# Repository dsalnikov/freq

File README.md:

# This is a KiCad project of ESC power board 

This is a board with power MOSFETs (any TO-252), drivers (L6390), and measurement circuits for current and voltage. 
All components are quite big, so board can be hand soldered.

### Known issues:
* There is no input voltage measurement
* Input voltage capacitors are too small

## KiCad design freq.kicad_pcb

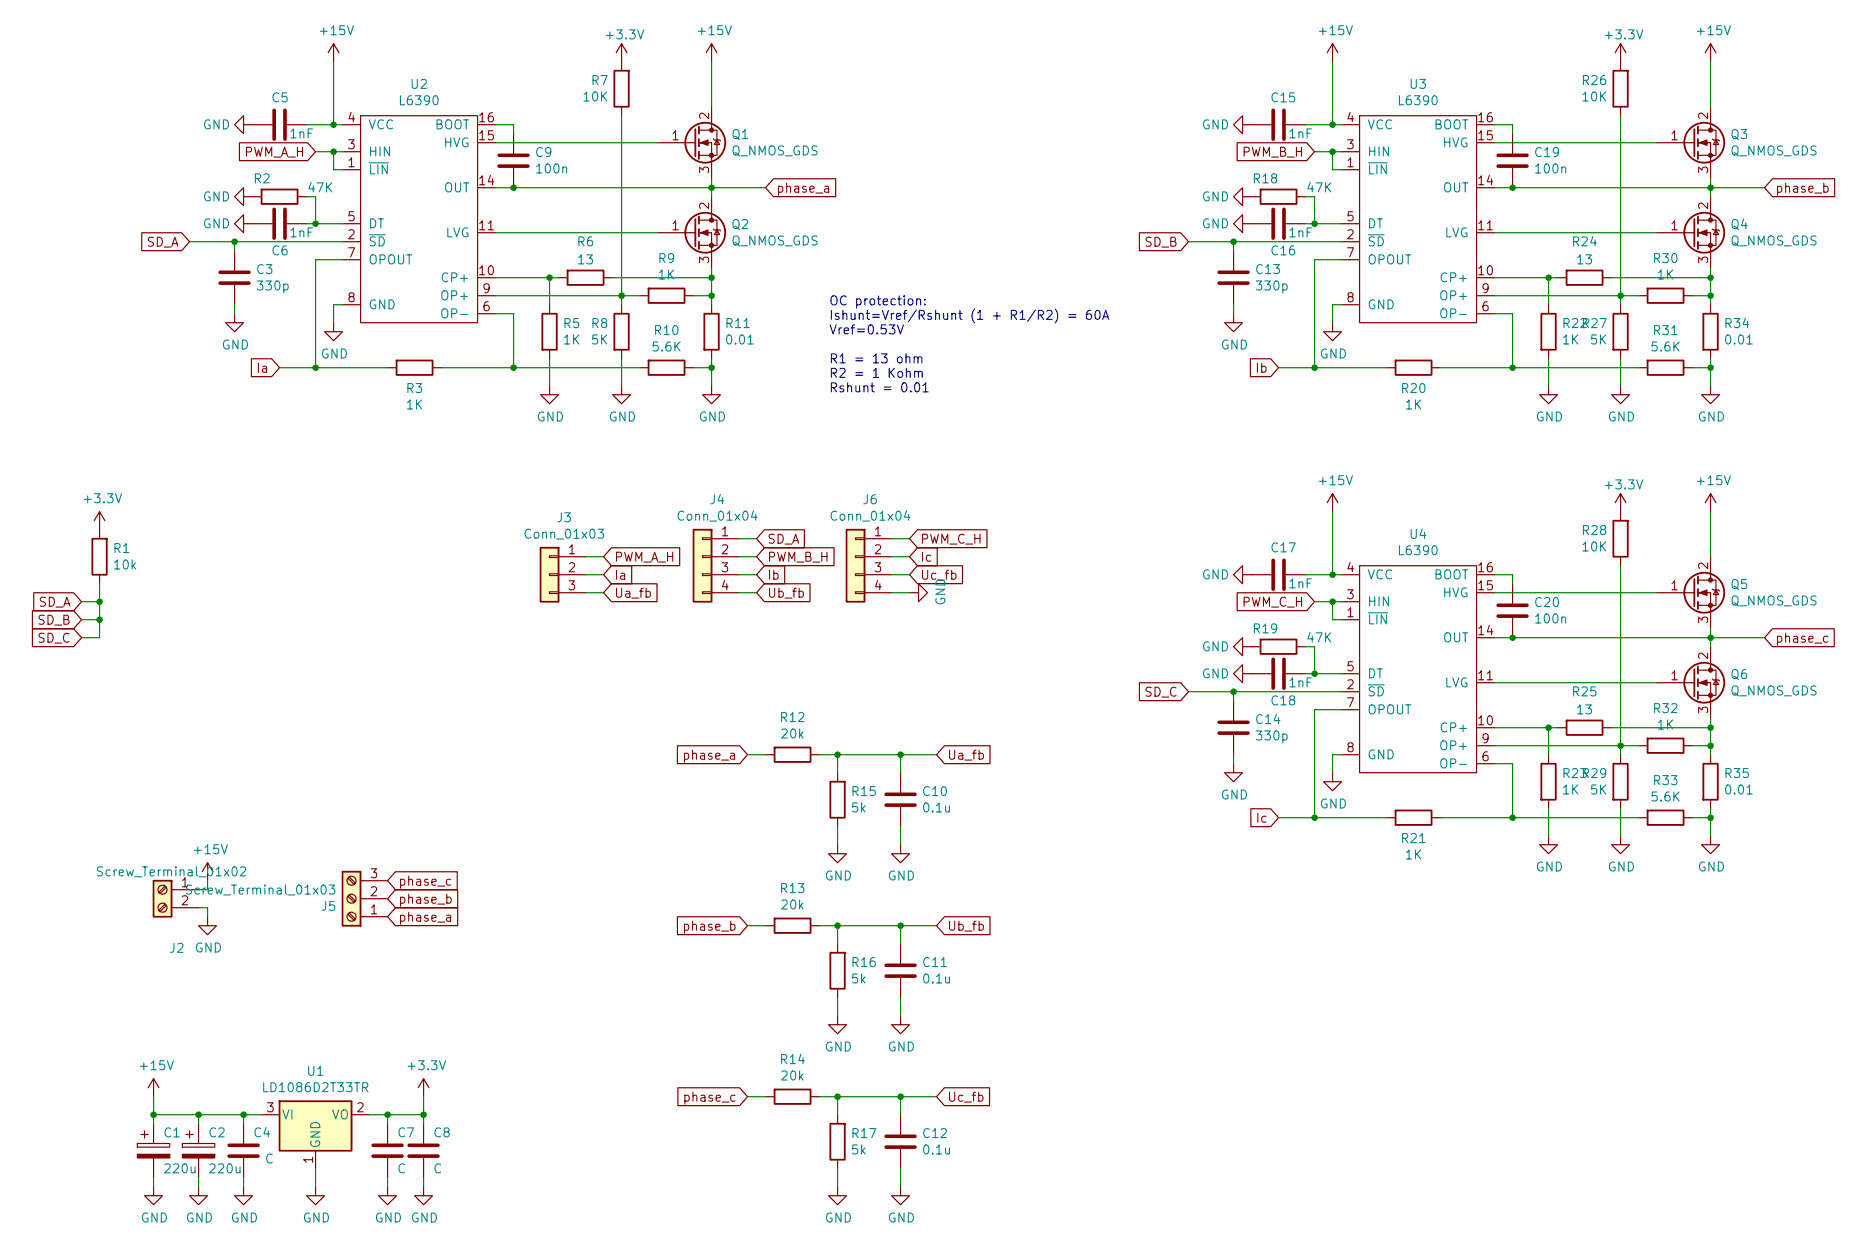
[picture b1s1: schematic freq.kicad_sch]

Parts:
C1, C2: 220u; CP_Elec_5x4.5
C3, C13, C14: 330p; C_0805_2012Metric_Pad1.15x1.40mm_HandSolder
C4, C7, C8: C; C_0805_2012Metric_Pad1.15x1.40mm_HandSolder
C5, C6, C15, C16, C17, C18: 1nF; C_0805_2012Metric_Pad1.15x1.40mm_HandSolder
C9, C19, C20: 100n; C_0805_2012Metric_Pad1.15x1.40mm_HandSolder
C10, C11, C12: 0.1u; C_0805_2012Metric_Pad1.15x1.40mm_HandSolder
J2: Screw_Terminal_01x02; TerminalBlock_Altech_AK300-2_P5.00mm
J3: Conn_01x03; PinHeader_1x03_P2.54mm_Vertical
J4, J6: Conn_01x04; PinHeader_1x04_P2.54mm_Vertical
J5: Screw_Terminal_01x03; TerminalBlock_Altech_AK300-3_P5.00mm
Q1, Q2, Q3, Q4, Q5, Q6: Q_NMOS_GDS; TO-252-2
R1: 10k; R_0805_2012Metric_Pad1.15x1.40mm_HandSolder
R2, R18, R19: 47K; R_0805_2012Metric_Pad1.15x1.40mm_HandSolder
R3, R5, R9, R20, R21, R22, R23, R30, R32: 1K; R_0805_2012Metric_Pad1.15x1.40mm_HandSolder
R6, R24, R25: 13; R_0805_2012Metric_Pad1.15x1.40mm_HandSolder
R7, R26, R28: 10K; R_0805_2012Metric_Pad1.15x1.40mm_HandSolder
R8, R27, R29: 5K; R_0805_2012Metric_Pad1.15x1.40mm_HandSolder
R10, R31, R33: 5.6K; R_0805_2012Metric_Pad1.15x1.40mm_HandSolder
R11, R34, R35: 0.01; R_2512_6332Metric_Pad1.52x3.35mm_HandSolder
R12, R13, R14: 20k; R_0805_2012Metric_Pad1.15x1.40mm_HandSolder
R15, R16, R17: 5k; R_0805_2012Metric_Pad1.15x1.40mm_HandSolder
U1: LD1086D2T33TR; SOT-223-3_TabPin2
U2, U3, U4: L6390; SOIC-16_3.9x9.9mm_P1.27mm

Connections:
+3V3: C7.1, C8.1, R1.2, R7.2, R26.2, R28.2, U1.2 (VO)
+15V: C1.1, C2.1, C4.1, C5.1, C15.1, C17.1, J2.1, Q1.2 (D), Q3.2 (D), Q5.2 (D), U1.3 (VI), U2.4 (VCC), U3.4 (VCC), U4.4 (VCC)
GND: C1.2, C2.2, C3.2, C4.2, C5.2, C6.2, C7.2, C8.2, C10.2, C11.2, C12.2, C13.2, C14.2, C15.2, C16.2, C17.2, C18.2, J2.2, J6.4, R2.2, R5.2, R8.2, R10.1, R11.2, R15.1, R16.1, R17.1, R18.2, R19.2, R22.2, R23.2, R27.2, R29.2, R31.1, R33.1, R34.2, R35.2, U1.1 (GND), U2.8 (GND), U3.8 (GND), U4.8 (GND)
Ia: J3.2, R3.2, U2.7 (OPOUT)
Ib: J4.3, R20.2, U3.7 (OPOUT)
Ic: J6.2, R21.2, U4.7 (OPOUT)
unnamed: C6.1, R2.1, U2.5 (DT)
unnamed: C9.1, U2.16 (BOOT)
unnamed: C16.1, R18.1, U3.5 (DT)
unnamed: C18.1, R19.1, U4.5 (DT)
unnamed: C19.1, U3.16 (BOOT)
unnamed: C20.1, U4.16 (BOOT)
unnamed: Q1.1 (G), U2.15 (HVG)
unnamed: Q2.1 (G), U2.11 (LVG)
unnamed: Q2.3 (S), R6.1, R9.1, R11.1
unnamed: Q3.1 (G), U3.15 (HVG)
unnamed: Q4.1 (G), U3.11 (LVG)
unnamed: Q4.3 (S), R24.1, R30.1, R34.1
unnamed: Q5.1 (G), U4.15 (HVG)
unnamed: Q6.1 (G), U4.11 (LVG)
unnamed: Q6.3 (S), R25.1, R32.1, R35.1
unnamed: R5.1, R6.2, U2.10 (CP+)
unnamed: R7.1, R8.1, R9.2, U2.9 (OP+)
unnamed: R3.1, R10.2, U2.6 (OP-)
unnamed: R20.1, R31.2, U3.6 (OP-)
unnamed: R21.1, R33.2, U4.6 (OP-)
unnamed: R22.1, R24.2, U3.10 (CP+)
unnamed: R23.1, R25.2, U4.10 (CP+)
unnamed: R26.1, R27.1, R30.2, U3.9 (OP+)
unnamed: R28.1, R29.1, R32.2, U4.9 (OP+)
PWM_A_H: J3.1, U2.1 (~LIN), U2.3 (HIN)
PWM_B_H: J4.2, U3.1 (~LIN), U3.3 (HIN)
PWM_C_H: J6.1, U4.1 (~LIN), U4.3 (HIN)
SD_A: C3.1, C13.1, C14.1, J4.1, R1.1, U2.2 (~SD), U3.2 (~SD), U4.2 (~SD)
Ua_fb: C10.1, J3.3, R12.1, R15.2
Ub_fb: C11.1, J4.4, R13.1, R16.2
Uc_fb: C12.1, J6.3, R14.1, R17.2
phase_a: C9.2, J5.1, Q1.3 (S), Q2.2 (D), R12.2, U2.14 (OUT)
phase_b: C19.2, J5.2, Q3.3 (S), Q4.2 (D), R13.2, U3.14 (OUT)
phase_c: C20.2, J5.3, Q5.3 (S), Q6.2 (D), R14.2, U4.14 (OUT)

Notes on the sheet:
OC protection: Ishunt=Vref/Rshunt (1 + R1/R2) = 60A Vref=0.53V R1 = 13 ohm R2 = 1 Kohm Rshunt = 0.01

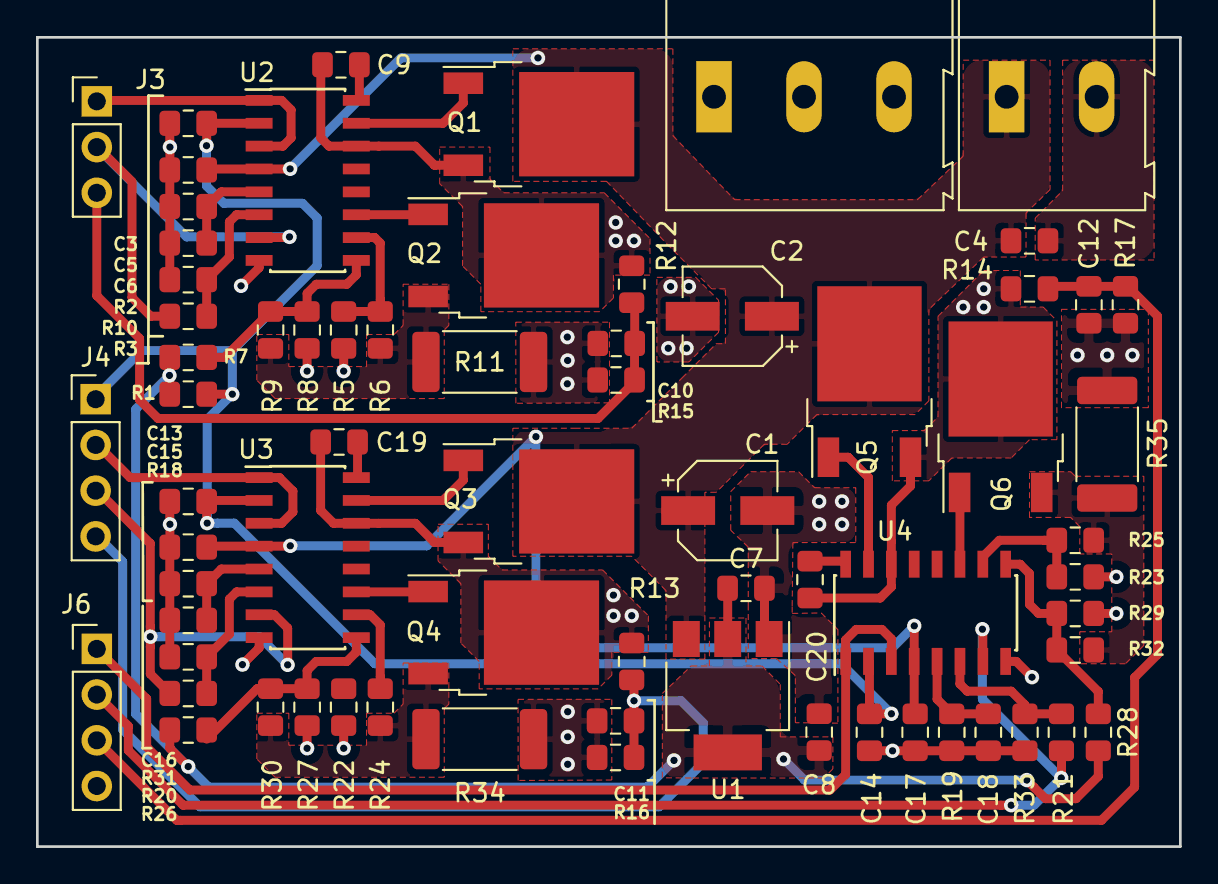
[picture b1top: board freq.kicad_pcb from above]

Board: 2 copper layers, 63.5 x 45.0 mm, 69 parts (0 on the bottom side), 40 nets.

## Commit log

2020-06-29 uploaded project files
2023-11-20 Add GitHub Actions example
2023-11-20 Rename main.yml to main.yml
2023-11-20 update kicad version
2023-11-20 add kicad-rescue symbols
